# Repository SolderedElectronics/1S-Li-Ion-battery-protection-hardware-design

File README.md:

# 1S Li-Ion battery protection Hardware Design

## About the Product

|  |
| :----------------------------------------------------------: |
| [Buy 1S Li-Ion battery protection](https://www.solde.red/333049) |

A battery protector is, simply put, a device that makes sure that something bad doesn’t happen to the battery. This small circuit board protects your lithium battery (of any capacity) from overcharge, overdischarge, overcurrent and short circuit. It has a JST connector for connecting the battery, and the battery can be directly soldered.

---

## Repository Contents

This repository contains all design files for 1S Li-Ion battery protection, organized as follows:

- **`CAD` folder**: Contains KiCAD design files, including:
  - Schematics
  - PCB layout
  - Panel PCB layout
  - Source 3D files in Fusion360, if any
  - All files are sorted by version with a detailed change log.
- **`OUTPUTS` folder**: Includes all production-ready files, such as:
  - Bill of Materials (BOM) and interactive BOM (iBOM)
  - PDF versions of schematics
  - 3D `.step` file of the board
  - 3D-printable models
  - Gerber files for PCB manufacturing
  - Image of the pinout of the board
  - Product image
  - Compliance, legal and generic sales documents

Refer to the `Change Log` in the CAD folder for details about updates between versions.

---

## Learn More About the Product

Beyond the repository, explore the following resources:

### Soldered Verify

The **Soldered Verify** system ensures every board you purchase from Soldered is fully functional. It also provides access to exclusive test data for your product. To get started, find the unique Soldered Verify ID on your product's packaging and enter the ID on the [Soldered Verify page](https://soldered.com/verify/) to access test results and additional product details.

### Soldered Community

Soldered Community is your go-to place for technical support. Our engineers track and answer all questions posted there, and it’s a great space for the maker community. Get answers to your questions and solutions for your challenges at [Soldered Community](https://soldered.com/community).

### solde.red

solde.red is an ultimate URL shortener and information hub. Access it by typing solde.red/ followed by your product SKU, e.g., [solde.red/333000](https://solde.red/333000), to find getting-started guides, datasheets, open-source hardware and software files, certifications, images, pinouts, and more. Read more about the shortener [here](https://solde.red/info/).

---

## Contributing

Contributions are welcome! Here’s how you can get involved:

- Submit pull requests to enhance the design or fix issues.
- Report bugs or problems by opening an issue.

We encourage community collaboration to make this product even better.

---

## About Soldered

[Soldered for Makers](https://soldered.com) specializes in designing and manufacturing electronic products tailored for enthusiasts, ranging from hobbyists to professionals. Our portfolio includes electronic boards, sensors, and actuators that are widely utilized in fields such as microelectronics, mechatronics, robotics, programming, and IoT. Every product we offer is designed in-house and built upon open-source hardware and software platforms. Proudly certified and manufactured within the European Union, our catalog likely includes the product you need for your project.

We complement these products with comprehensive tutorials and manuals, product descriptions, schematics, programming codes, and project examples. Our round-the-clock [customer and technical support](https://soldered.com/community) is available for all our products, irrespective of the sales channel. Soldered’s success and services reflect our maker community’s unwavering [trust](https://www.trustpilot.com/review/soldered.com), for which we are deeply grateful. Join our community and create using Soldered products.

---

## License

All Soldered open-source hardware (OSH) is under The TAPR Open Hardware License. Read more in the LICENSE file located in this repository.

**Disclaimer:**

No warranty - all designs in this repository are distributed in the hope that they will be useful, but without any warranty. They are provided "AS IS", therefore without warranty of any kind, either expressed or implied. The entire quality and performance of what you do with the contents of this repository are your responsibility. In no event Soldered Electronics will be liable for your damages, or losses, including any general, special, incidental, or consequential damage arising out of the use or inability to use the contents of this repository. 

---

## Have fun!

Thank you for your support from your fellow makers at Soldered Electronics.

Happy Making!

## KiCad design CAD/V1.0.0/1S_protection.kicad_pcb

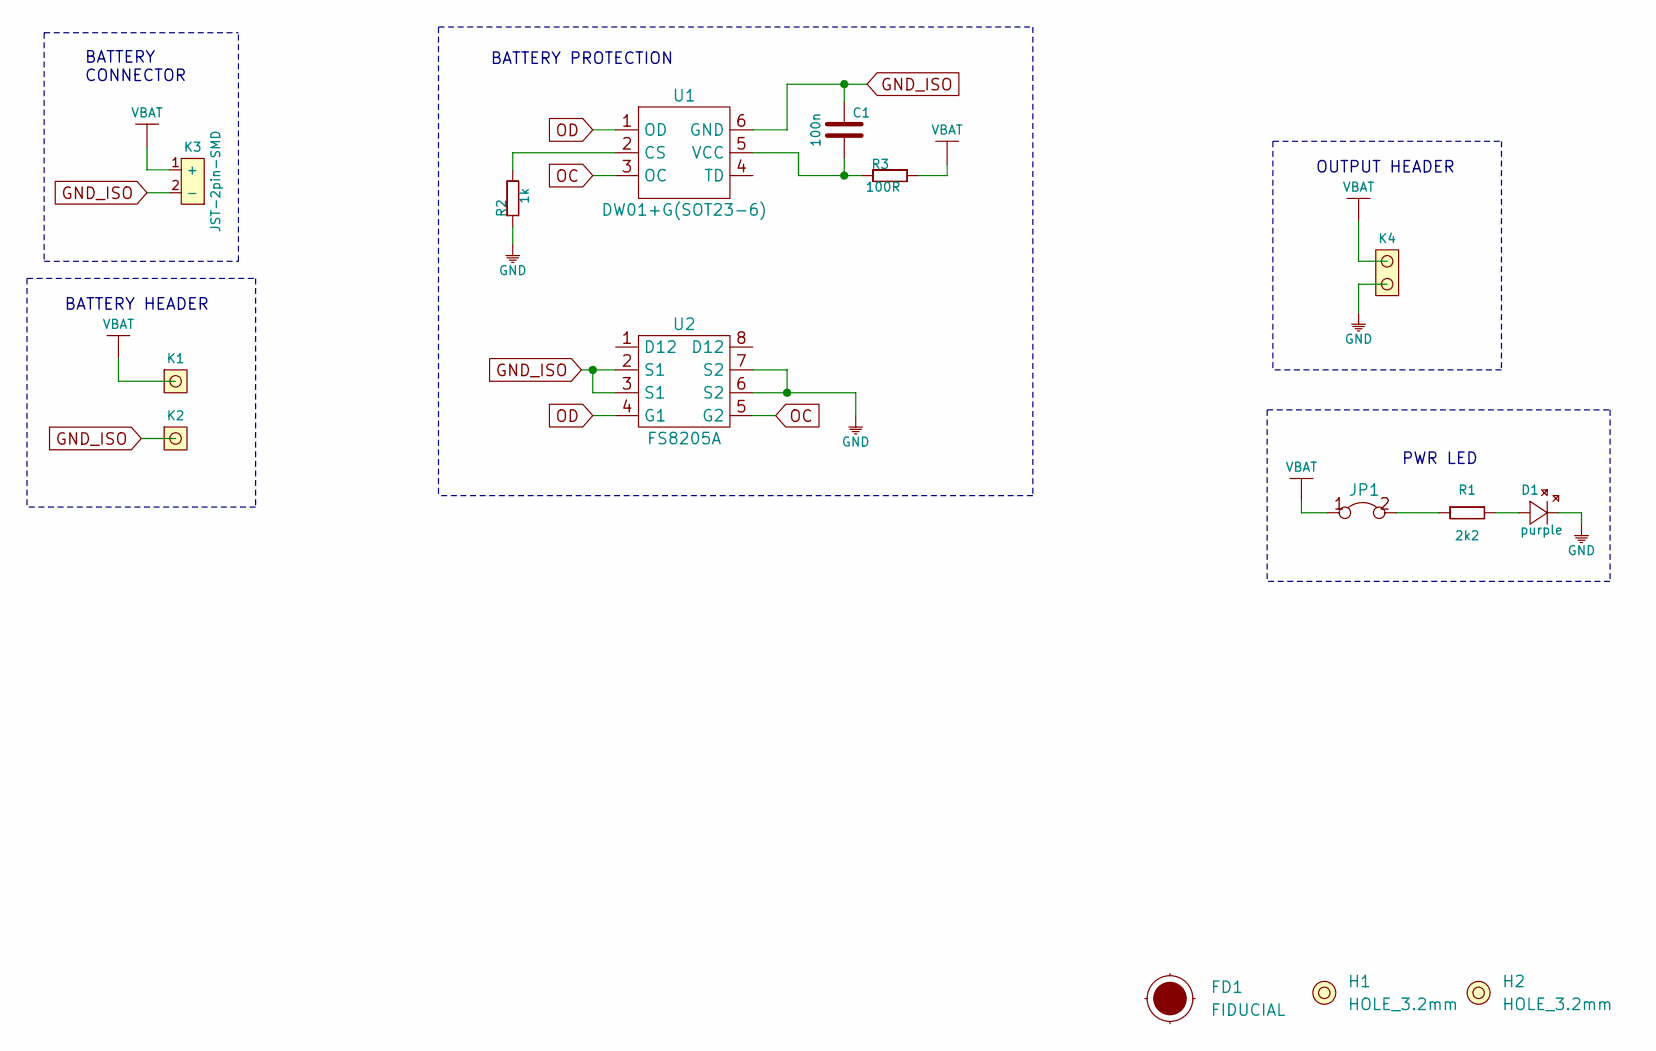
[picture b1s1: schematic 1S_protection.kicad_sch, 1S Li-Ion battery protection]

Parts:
C1: 100n; 0603C
D1: purple; 0402LED
FD1: FIDUCIAL; FIDUCIAL_23
H1, H2: HOLE_3.2mm
JP1: SMD-JUMPER-CONNECTED_TRACE_SLODERMASK
K1, K2: HEADER_MALE_1X1
K3: JST-2pin-SMD
K4: HEADER_MALE_2X1
R1: 2k2; 0402R
R2: 1k; 0603R
R3: 100R; 0603R
U1: DW01+G(SOT23-6); Sot23-6
U2: FS8205A; TSSOP8

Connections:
GND: D1.2 (K), K4.1, R2.1, U2.6 (S2), U2.7 (S2)
GND_ISO: C1.2, K2.1, K3.2 (-), U1.6 (GND), U2.2 (S1), U2.3 (S1)
unnamed: C1.1, R3.1, U1.5 (VCC)
unnamed: D1.1 (A), R1.2
unnamed: JP1.2, R1.1
unnamed: R2.2, U1.2 (CS)
OC: U1.3 (OC), U2.5 (G2)
OD: U1.1 (OD), U2.4 (G1)
VBAT: JP1.1, K1.1, K3.1 (+), K4.2, R3.2

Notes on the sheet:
OUTPUT HEADER
PWR LED
BATTERY PROTECTION
BATTERY CONNECTOR
BATTERY HEADER

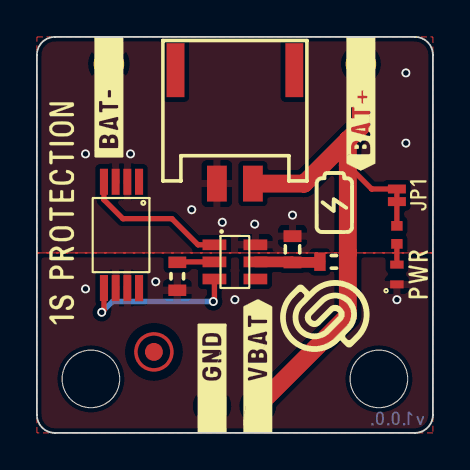
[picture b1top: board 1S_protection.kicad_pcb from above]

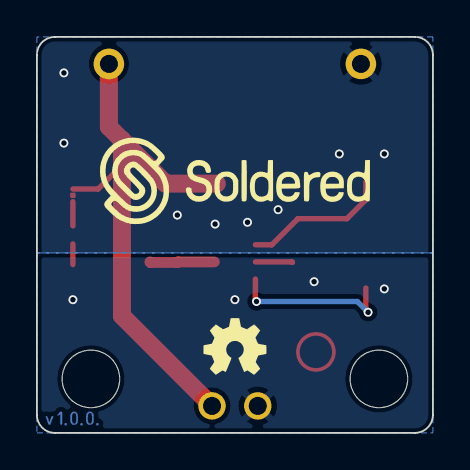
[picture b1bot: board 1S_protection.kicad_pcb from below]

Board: 2 copper layers, 22.0 x 22.0 mm, 16 parts (4 on the bottom side), 9 nets.

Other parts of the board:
Ref**: Val**; Version1.0.0.

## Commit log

2022-08-06 Updating open source files.
